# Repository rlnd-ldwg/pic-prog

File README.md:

# Programmer for 8-bit PIC devices built upon AVR (or Arduino)

For [Micro progmeter](https://github.com/jaromir-sukuba/micro_progmeter) project I want to deliver full set of open-source materials, but it would be shame if folks trying to replicate the project would have to buy another programmer to flash the PIC MCU, so I decided to do a little bit of brain stretching and implement PIC16F1xxx programmer with... Arduino. I really can't say I love this platform, but it is low cost and available.
Together with SDCC compiler this serves as completely open-source basis for many 8-bit PIC devices.

The current project status: Programmer working, sources need cleanup, perhaps rework of its structure (it grew out of its simple structure).
# List of supported devices is at the end of this page.

## Hardware
There are two options fo hardware for this project:

### Hardware option 1 - Arduino hardware
Take any Arduino with ATmega328P, like Uno or most of cheap chinese knock-off boards. Considering the target has its own power supply, connect GND, MCLR, PGC and PGD lines to respective pins on arduino as follows:

| Arduino pin | AVR pin | Target PIC pin | Comment                                                                     |
|-------------|---------|----------------|-----------------------------------------------------------------------------|
| GND         | GND     | GND            | common ground                                                               |
| 5V          | VDD     | VDD            | optional*- power supply for PIC MCU, you may power target from other source |
| A3          | PC3     | MCLR           | reset line of PIC MCU                                                       |
| A1          | PC1     | PGD            | programming data line                                                       |
| A0          | PC0     | PGC            | programming clock line                                                      |

* If you are powering target PIC from other power source (in circuit programming), series resistors (something like 470-1000 Ohms) in MCLR, PGC and PGD lines are good idea, it will somehow decrease currents flowing through IO pins due to power supplies differences between arduino and target board. In this configuration, even targets running at 3,3V are possible to program, though it is dirty practice.

Power it up, no smoke should be released. Run arduino IDE, open programmer firmware from here (/fw/pp.ino), complie and upload to arduino board - now you have PIC programmer ready to go. Go to software below.

The programmer is proven to work with some generic Uno board from china, as well as chinese arduino-nano clone

#### High Voltage Programming
Basically copied from https://github.com/rweather/ardpicprog and only implemented for Arduino Uno and `CF_P16F_A`. Needs the transistor and resistors from https://rweather.github.io/ardpicprog/pic14_zif_circuit.html (tested only for 16f1825: 9V block battery as power source, BC 337, 1k for the base and 10k for the emitter) and these connections to the Arduino:

| Arduino pin | AVR pin | Target pin / comment          |
|-------------|---------|-------------------------------|
| GND         | GND     | GND/VSS                       |
| A0          | PC0     | PGC                           |
| A1          | PC1     | PGD                           |
| A2          | PC2     | VDD                           |
| A4          | PC4     | MCLR transistor base resistor |

### Hardware option 2 - dedicated board
I designed this little board, see at /hw directory

Considering the target has its own power supply, connect GND, MCLR, PGC and PGD lines to respective pins on PIC programmer (notice the pinout similar to PICkit programmers). Vdd line is not currently used ad it is not needed for operation of programmer, but future revisions of firmware may take advantage of this pin and detect target VDD.
The hardware works with both FT232RL and CY7C65213 in place of USB/serial converter. Both were proven to work, with no other hardware difference.

Use [another arduino](https://www.arduino.cc/en/Tutorial/ArduinoISP) (or proper ISP programmer) to load Arduino UNO bootloader to PIC programmer board (performed only once), turning it into regular arduino compatible board.

Ensure JP2 is closed, then you can load new firmware into PIC programmer using regular Arduino IDE. Open jumper JP2. Now you have your programmer ready to go, move on to software.
The firmware should be able to compile outside Arduino IDE as it doesn't contain any Arduino-specific stuff, though I haven't tried that.

## Software

When running under Linux, download source from this repository and run

`gcc -Wall pp3.c -o pp3`

This should build executable pp3. When working under windows, you can download compiled binary from this repository. Alternatively, you can build it from source - install minGW and run

`gcc -Wall pp3.c -o pp3`

ie. the same procedure as on Linux. This should result in silent build with pp3.exe executable created.

Running the executable with no parameters should only bring banner "pp programmer". Though running with basic set of parameters

`./pp3 -c /dev/ttyACM0 -t 16f1829 file.hex`

under Linux, where -c parameter denotes port to be accessed, -t parameter defines PIC to be programmed and last parameter is hex file to be downloaded; or

`pp3.exe -c COM30 -t 16f1829 file.hex`

under Windows should program the target PIC; with expected result:

	$ ./pp3 -c /dev/ttyACM0 -t 16f1829 file.hex
    Opening serial port
    Device ID 0x27E4
    Programming FLASH (16384 B in 256 pages)
    Programming config
    Verifying FLASH (16384 B in 256 pages)
    Verifying config
    Releasing MCLR

## Notes on software

If you are running the hardware on generic arduino board or you forget to open jumper JP2 after loading firmware on dedicated hardware, you may need to insert waiting time after opening serial port and before communication - to ensure Arduino bootloader times out after opening serial port and takes control to programmer firmware. It should look like this

`pp3.exe -c COM30 -s 1700 -t 16f1829 file.bin`

where number after -s switch defines the number of miliseconds to wait after opening the serial port.

You may omit the actual programming using -p switch or verification using -n switch, when using both the programmer only checks target device signature and exits.

`$ ./pp3 -c /dev/ttyACM0 -p -n -t 16f1829 file.bin`

    Opening serial port
    Device ID 0x27E4
    Releasing MCLR

you can add some debug output info using -v parameter, ranging from -v 1 to -v 4. It may be suitable for debugging, -v 4 prints out all byte transaction on serial port, so be prepared for huge output.
There is database file pp3_devices.dat which hold information of supported PIC types. For now, the filename is fixed in code can't be changed and file has to be in the same directory as pp executable..

## Supported devices

Obviously, there is more supported than verified (tested) devices. I tried to test at least one device from specific family. The members from one family are usually very very similar, giving me enough confidence to mark them as supproted. Of course, typos can happen, but those are easy to correct.

**DEVICE**|**TESTED**
:-----:|:-----:
PIC12F1501|YES
PIC12F1571| 
PIC12F1572|YES
PIC12F1612|YES
PIC12F1822|YES
PIC12F1840|YES
PIC12LF1501|YES
PIC12LF1552|YES
PIC12LF1571| 
PIC12LF1572| 
PIC12LF1612| 
PIC12LF1822| 
PIC12LF1840|YES
PIC16F1454| 
PIC16F1455|YES
PIC16F1459| 
PIC16F1503|YES
PIC16F1507|YES
PIC16F1508| 
PIC16F1509|YES
PIC16F1512| 
PIC16F1513| 
PIC16F1516|YES
PIC16F1517| 
PIC16F1518| 
PIC16F1519| 
PIC16F1528| 
PIC16F1529| 
PIC16F15313| 
PIC16F15323| 
PIC16F15324| 
PIC16F15325| 
PIC16F15344| 
PIC16F15345| 
PIC16F15354| 
PIC16F15355|YES
PIC16F15356| 
PIC16F15375| 
PIC16F15376| 
PIC16F15385| 
PIC16F15386| 
PIC16F1574| 
PIC16F1575|YES
PIC16F1578| 
PIC16F1579| 
PIC16F1613|YES
PIC16F1614| 
PIC16F1615|YES
PIC16F1618| 
PIC16F1619|YES
PIC16F1703|YES
PIC16F1704| 
PIC16F1705| 
PIC16F1707| 
PIC16F1708| 
PIC16F1709| 
PIC16F1713| 
PIC16F1716| 
PIC16F1717| 
PIC16F1718|YES
PIC16F1719| 
PIC16F1764| 
PIC16F1765|YES
PIC16F1768| 
PIC16F1769| 
PIC16F1782| 
PIC16F1783|YES
PIC16F1784| 
PIC16F1786| 
PIC16F1787| 
PIC16F1788|YES
PIC16F1789| 
PIC16F1823|YES 
PIC16F1824| 
PIC16F1825|YES 
PIC16F1826| 
PIC16F1827| 
PIC16F1828| 
PIC16F1829|YES
PIC16F18313| 
PIC16F18323| 
PIC16F18324| 
PIC16F18325| 
PIC16F18326| 
PIC16F18344| 
PIC16F18345| 
PIC16F18346|YES
PIC16F18424| 
PIC16F18425| 
PIC16F18426| 
PIC16F18444| 
PIC16F18445| 
PIC16F18446| 
PIC16F18455| 
PIC16F18456| 
PIC16F1847| 
PIC16F18854| 
PIC16F18855|YES
PIC16F18856| 
PIC16F18857| 
PIC16F18875|YES
PIC16F18876| 
PIC16F18877| 
PIC16F19155| 
PIC16F19156|YES
PIC16F19175| 
PIC16F19176|YES
PIC16F19185| 
PIC16F19186| 
PIC16F19195| 
PIC16F19196| 
PIC16F19197| 
PIC16F1933|YES
PIC16F1934| 
PIC16F1936| 
PIC16F1937| 
PIC16F1938| 
PIC16F1939| 
PIC16F1946| 
PIC16F1947| 
PIC16LF1454| 
PIC16LF1455|YES
PIC16LF1459| 
PIC16LF1503|YES
PIC16LF1507| 
PIC16LF1508|YES
PIC16LF1509| 
PIC16LF1512| 
PIC16LF1513| 
PIC16LF1516| 
PIC16LF1517| 
PIC16LF1518| 
PIC16LF1519| 
PIC16LF1528| 
PIC16LF1529| 
PIC16LF15313| 
PIC16LF15323| 
PIC16LF15324| 
PIC16LF15325| 
PIC16LF15344| 
PIC16LF15345| 
PIC16LF15354| 
PIC16LF15355| 
PIC16LF15356| 
PIC16LF15375| 
PIC16LF15376| 
PIC16LF15385| 
PIC16LF15386| 
PIC16LF1574| 
PIC16LF1575| 
PIC16LF1578| 
PIC16LF1579| 
PIC16LF1613| 
PIC16LF1614| 
PIC16LF1615| 
PIC16LF1618| 
PIC16LF1619|
PIC16LF1703| 
PIC16LF1704|YES
PIC16LF1705| 
PIC16LF1707| 
PIC16LF1708| 
PIC16LF1709| 
PIC16LF1713|YES
PIC16LF1716| 
PIC16LF1717| 
PIC16LF1718| 
PIC16LF1719| 
PIC16LF1764| 
PIC16LF1765| 
PIC16LF1768| 
PIC16LF1769| 
PIC16LF1782| 
PIC16LF1783| 
PIC16LF1784| 
PIC16LF1786| 
PIC16LF1787| 
PIC16LF1788| 
PIC16LF1789| 
PIC16LF1824| 
PIC16LF1825| 
PIC16LF1826| 
PIC16LF1827| 
PIC16LF1828| 
PIC16LF1829|YES
PIC16LF18313| 
PIC16LF18323| 
PIC16LF18324| 
PIC16LF18325| 
PIC16LF18326| 
PIC16LF18344| 
PIC16LF18345| 
PIC16LF18346| 
PIC16LF18424| 
PIC16LF18425| 
PIC16LF18444| 
PIC16LF18445| 
PIC16LF18455| 
PIC16LF18456| 
PIC16LF1847| 
PIC16LF18854| 
PIC16LF18855| 
PIC16LF18856| 
PIC16LF18857| 
PIC16LF18875| 
PIC16LF18876| 
PIC16LF18877| 
PIC16LF1902| 
PIC16LF1903|YES
PIC16LF1904| 
PIC16LF1906| 
PIC16LF1907| 
PIC16LF19155| 
PIC16LF19156| 
PIC16LF19175| 
PIC16LF19176| 
PIC16LF19185| 
PIC16LF19186| 
PIC16LF19195| 
PIC16LF19196| 
PIC16LF19197| 
PIC16LF1933| 
PIC16LF1934| 
PIC16LF1936| 
PIC16LF1937| 
PIC16LF1938| 
PIC16LF1939| 
PIC16LF1946| 
PIC16LF1947| 
PIC18F23K22| 
PIC18F24J10|YES
PIC18F24J11| 
PIC18F24J50|YES
PIC18F24K22|YES
PIC18F24K40| 
PIC18F24K42| 
PIC18F24K50| 
PIC18F25J10| 
PIC18F25J11| 
PIC18F25J50| 
PIC18F25K22| 
PIC18F25K40| 
PIC18F25K42| 
PIC18F25K50|YES
PIC18F25K80|YES
PIC18F25Q10|YES
PIC18F26J11|YES
PIC18F26J13| 
PIC18F26J50|YES
PIC18F26J53| 
PIC18F26K22|YES
PIC18F26K40| 
PIC18F26K42| 
PIC18F26K50| 
PIC18F26K80| 
PIC18F26Q10| 
PIC18F27J13| 
PIC18F27J53|YES
PIC18F27K40| 
PIC18F27K42| 
PIC18F27Q10| 
PIC18F43K22| 
PIC18F44J10| 
PIC18F44J11| 
PIC18F44J50| 
PIC18F44K22| 
PIC18F45J10|YES
PIC18F45J11| 
PIC18F45J50| 
PIC18F45K22| 
PIC18F45K40| 
PIC18F45K42| 
PIC18F45K50| 
PIC18F45K80| 
PIC18F45Q10| 
PIC18F46J11| 
PIC18F46J13| 
PIC18F46J50| 
PIC18F46J53| 
PIC18F46K22| 
PIC18F46K40| 
PIC18F46K42| 
PIC18F46K50| 
PIC18F46K80| 
PIC18F46Q10| 
PIC18F47J13| 
PIC18F47J53| 
PIC18F47K40|YES
PIC18F47K42| 
PIC18F47Q10| 
PIC18F47Q43|YES
PIC18F47Q83|YES
PIC18F47Q84|YES
PIC18F55K42| 
PIC18F56K42| 
PIC18F57K42|YES
PIC18F63J11| 
PIC18F63J90| 
PIC18F64J11| 
PIC18F64J90| 
PIC18F65J10| 
PIC18F65J11| 
PIC18F65J15| 
PIC18F65J50| 
PIC18F65J90| 
PIC18F65J94| 
PIC18F65K22| 
PIC18F65K40| 
PIC18F65K80| 
PIC18F65K90| 
PIC18F66J10| 
PIC18F66J11| 
PIC18F66J15|YES
PIC18F66J16| 
PIC18F66J50| 
PIC18F66J55| 
PIC18F66J60| 
PIC18F66J65| 
PIC18F66J90| 
PIC18F66J93| 
PIC18F66J94| 
PIC18F66J99| 
PIC18F66K22| 
PIC18F66K40| 
PIC18F66K80| 
PIC18F66K90| 
PIC18F67J10| 
PIC18F67J11| 
PIC18F67J50|YES
PIC18F67J60| 
PIC18F67J90| 
PIC18F67J93| 
PIC18F67J94| 
PIC18F67K22|YES
PIC18F67K40| 
PIC18F67K90| 
PIC18F83J11| 
PIC18F83J90| 
PIC18F84J11| 
PIC18F84J90| 
PIC18F85J10| 
PIC18F85J11| 
PIC18F85J15| 
PIC18F85J50| 
PIC18F85J90| 
PIC18F85J94| 
PIC18F85K22| 
PIC18F85K90| 
PIC18F86J10| 
PIC18F86J11| 
PIC18F86J15| 
PIC18F86J16| 
PIC18F86J50| 
PIC18F86J55| 
PIC18F86J60| 
PIC18F86J65| 
PIC18F86J72| 
PIC18F86J90| 
PIC18F86J93| 
PIC18F86J94| 
PIC18F86J99| 
PIC18F86K22| 
PIC18F86K90| 
PIC18F87J10| 
PIC18F87J11| 
PIC18F87J50| 
PIC18F87J60| 
PIC18F87J72| 
PIC18F87J90| 
PIC18F87J93| 
PIC18F87J94| 
PIC18F87K22| 
PIC18F87K90| 
PIC18F95J94| 
PIC18F96J60| 
PIC18F96J65| 
PIC18F96J94| 
PIC18F96J99| 
PIC18F97J60| 
PIC18F97J94| 
PIC18LF23K22| 
PIC18LF24J10| 
PIC18LF24J11| 
PIC18LF24J50| 
PIC18LF24K22| 
PIC18LF24K40| 
PIC18LF24K42| 
PIC18LF24K50|YES
PIC18LF25J10| 
PIC18LF25J11| 
PIC18LF25J50| 
PIC18LF25K22|YES
PIC18LF25K40| 
PIC18LF25K42| 
PIC18LF25K50|YES
PIC18LF25K80| 
PIC18LF26J11| 
PIC18LF26J13| 
PIC18LF26J50| 
PIC18LF26J53| 
PIC18LF26K22| 
PIC18LF26K40| 
PIC18LF26K42| 
PIC18LF26K50| 
PIC18LF26K80| 
PIC18LF27J13| 
PIC18LF27J53| 
PIC18LF27K40| 
PIC18LF27K42| 
PIC18LF43K22| 
PIC18LF44J10| 
PIC18LF44J11| 
PIC18LF44J50| 
PIC18LF44K22| 
PIC18LF45J10| 
PIC18LF45J11| 
PIC18LF45J50| 
PIC18LF45K22| 
PIC18LF45K40| 
PIC18LF45K42| 
PIC18LF45K50| 
PIC18LF45K80| 
PIC18LF46J11| 
PIC18LF46J13| 
PIC18LF46J50| 
PIC18LF46J53| 
PIC18LF46K22| 
PIC18LF46K40| 
PIC18LF46K42| 
PIC18LF46K50| 
PIC18LF46K80| 
PIC18LF47J13| 
PIC18LF47J53| 
PIC18LF47K40| 
PIC18LF47K42| 
PIC18LF55K42| 
PIC18LF56K42| 
PIC18LF57K42| 
PIC18LF65K40| 
PIC18LF65K80| 
PIC18LF66K40| 
PIC18LF66K80| 
PIC18LF67K40| 

The whole project is licensed under MIT license, see LICENSE.md file.
Some more details to be found here https://hackaday.io/project/8559-pic16f1xxx-arduino-based-programmer

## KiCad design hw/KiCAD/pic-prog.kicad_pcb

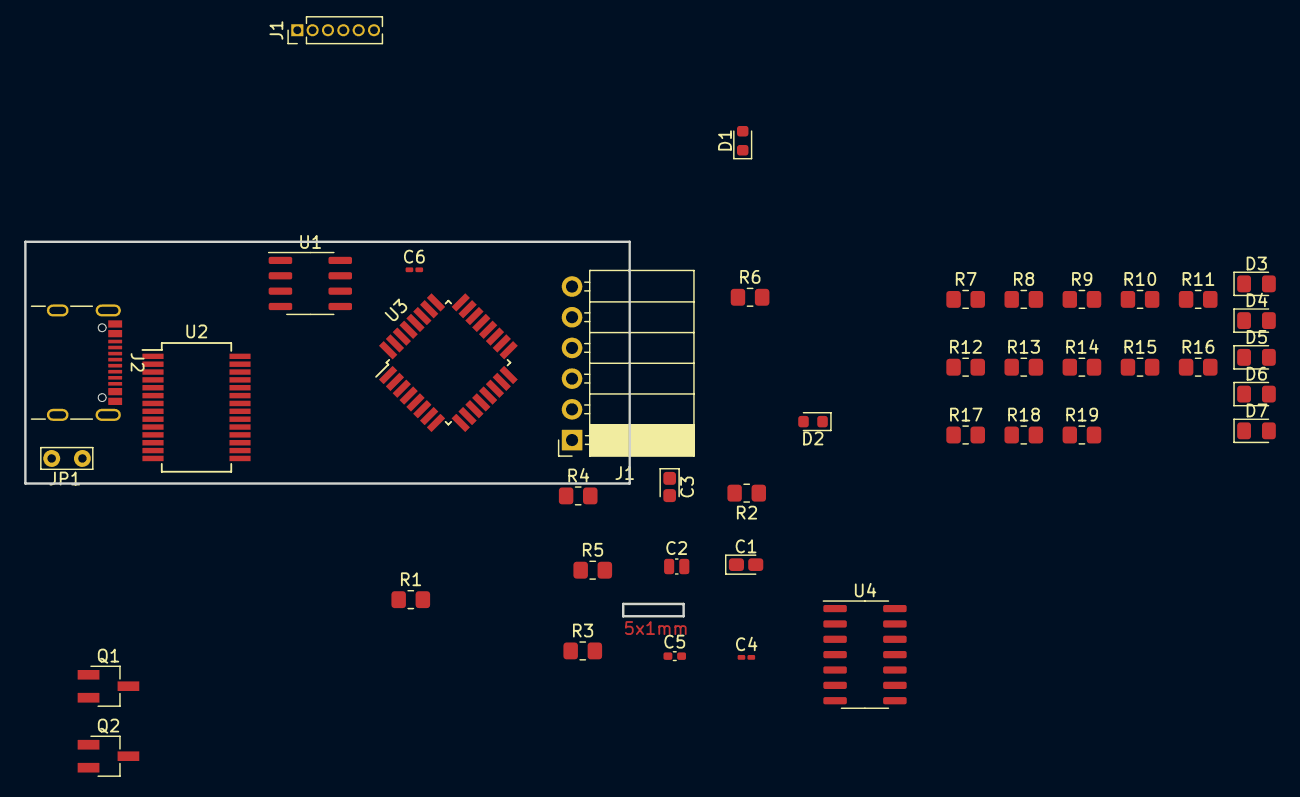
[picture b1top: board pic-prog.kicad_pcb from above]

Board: 2 copper layers, 42 parts (0 on the bottom side), 38 nets, no tracks yet.

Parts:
C1: 1µF; CP_EIA-1608-10_AVX-L_Pad1.25x1.05mm_HandSolder
C2: 1nF; C_0504_1310Metric_Pad0.83x1.28mm_HandSolder
C3: 1µF; CP_EIA-1608-08_AVX-J
C4: 100nF; C_0201_0603Metric_Pad0.64x0.40mm_HandSolder
C5: 100nF; C_0402_1005Metric_Pad0.74x0.62mm_HandSolder
C6: C; C_0201_0603Metric_Pad0.64x0.40mm_HandSolder
D1, D2: BAT43; D_0603_1608Metric
D3: Green; D_0805_2012Metric_Pad1.15x1.40mm_HandSolder
D4: Blue; D_0805_2012Metric_Pad1.15x1.40mm_HandSolder
D5: Red; D_0805_2012Metric_Pad1.15x1.40mm_HandSolder
D6: Orange; D_0805_2012Metric_Pad1.15x1.40mm_HandSolder
D7: White; D_0805_2012Metric_Pad1.15x1.40mm_HandSolder
J1: ICSP PIC; PinSocket_1x06_P2.54mm_Horizontal
J1#2: ISP AVR; PinHeader_1x06_P1.27mm_Vertical
J2: USB-C connector; USB_C_Receptacle_GCT_USB4105-xx-A_16P_TopMnt_Horizontal
JP1: bootloading; TestPoint_Bridge_Pitch2.54mm_Drill0.7mm
Q1, Q2: BS250; SC-59_Handsoldering
R1: 5k6; R_0805_2012Metric_Pad1.20x1.40mm_HandSolder
R2: 100; R_0805_2012Metric_Pad1.20x1.40mm_HandSolder
R3, R4, R7, R8, R9: 1k; R_0805_2012Metric_Pad1.20x1.40mm_HandSolder
R5, R6: 5k1; R_0805_2012Metric_Pad1.20x1.40mm_HandSolder
R10, R11, R12, R13: 470; R_0805_2012Metric_Pad1.20x1.40mm_HandSolder
R14, R15, R16, R17, R18, R19: R; R_0805_2012Metric_Pad1.20x1.40mm_HandSolder
U1: NE555D; SOIC-8_3.9x4.9mm_P1.27mm
U2: FT232RL; SSOP-28_5.3x10.2mm_P0.65mm
U3: ATmega328P-A; TQFP-32_7x7mm_P0.8mm
U4: 7403; SOIC-14_3.9x8.7mm_P1.27mm

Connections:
Gnd: C2.1, C2.2, C3.2, C4.2, D3.1 (K), J1.3, J1#2.6, J2.A1 (GND), J2.A12 (GND), J2.B1 (GND), J2.B12 (GND), J2.S1 (SHIELD), R1.1, R5.2, R6.2, R14.2, R18.2, U1.1 (GND), U1.2 (TR), U1.6 (THR), U2.7 (GND), U2.18 (GND), U2.21 (GND), U2.25 (AGND), U2.26 (TEST), U3.3 (GND), U3.5 (GND), U3.21 (GND), U4.7 (GND)
MCLR/Vpp: J1.1, Q1.1 (D), Q2.1 (D), R14.1
MISO: J1#2.1, U3.16 (PB4)
MOSI: J1#2.4, U3.15 (PB3)
unnamed: C1.2, R2.1
unnamed: C1.1, D1.1 (K), D2.2 (A)
unnamed: D3.2 (A), R7.2
unnamed: D4.2 (A), R8.1
unnamed: D4.1 (K), U2.22 (CBUS1)
unnamed: D5.2 (A), R9.1
unnamed: D5.1 (K), U2.23 (CBUS0)
unnamed: D6.1 (K), R17.1
unnamed: D7.1 (K), R18.1
unnamed: J2.A5 (CC1), R5.1
unnamed: J2.B5 (CC2), R6.1
unnamed: JP1.1 (A), U2.9 (DCR)
unnamed: Q1.2 (G), R16.2, U4.3
unnamed: R17.2, U4.2, U4.8
unnamed: R1.2, R2.2, U1.3 (Q)
unnamed: R4.1, U2.5 (RXD)
unnamed: R3.1, U2.1 (TXD)
unnamed: J2.A6 (D+), J2.B6 (D+), U2.15 (USBD+)
unnamed: J2.A7 (D-), J2.B7 (D-), U2.16 (USBD-)
unnamed: R3.2, U3.12 (PB0)
unnamed: R4.2, U3.13 (PB1)
unnamed: R10.1, U3.23 (PC0)
unnamed: R11.1, U3.24 (PC1)
unnamed: R12.1, U3.25 (PC2)
unnamed: R13.1, U3.26 (PC3)
PGC: J1.5, R10.2
PGD: J1.4, R11.2
PGM: J1.6, Q2.2 (G), R15.2, R19.2, U4.6, U4.11
Reset: C5.2, J1#2.5, U3.29 (~RESET/PC6)
SCK: J1#2.3, U3.17 (PB5)
Vcc: C4.1, D1.2 (A), D6.2 (A), J1.2, J1#2.2, J2.A4 (VBUS), J2.A9 (VBUS), J2.B4 (VBUS), J2.B9 (VBUS), Q1.3 (S), R7.1, R8.2, R9.2, R12.2, R15.1, R16.1, R19.1, U1.4 (R), U1.8 (VCC), U2.4 (VCCIO), U2.19 (~RESET), U2.20 (VCC), U3.4 (VCC), U3.6 (VCC), U3.18 (AVCC), U4.14 (VCC)
Vpp: C3.1, D2.1 (K), Q2.3 (S)
Vpp_on: D7.2 (A), U4.1, U4.4
Vpp_select: U4.5, U4.9, U4.10, U4.12, U4.13

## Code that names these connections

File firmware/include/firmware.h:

/*
 * firmware.h v1.0.0
 * 
 * Copyright October 2023 R.Ludwig
 * 
 * This program is free software; you can redistribute it and/or modify
 * it under the terms of the GNU General Public License as published by
 * the Free Software Foundation; either version 2 of the License, or
 * (at your option) any later version.
 * 
 * This program is distributed in the hope that it will be useful,
 * but WITHOUT ANY WARRANTY; without even the implied warranty of
 * MERCHANTABILITY or FITNESS FOR A PARTICULAR PURPOSE.  See the
 * GNU General Public License for more details.
 * 
 * You should have received a copy of the GNU General Public License
 * along with this program; if not, write to the Free Software
 * Foundation, Inc., 51 Franklin Street, Fifth Floor, Boston,
 * MA 02110-1301, USA.
 * 
 * constant and macro definition for main program
 * 
 * initial version 2023/10/26
 * 
 */
 
#ifndef FW_H
#define FW_H

#define ISP_PORT  PORTC
#define ISP_DDR   DDRC
#define ISP_PIN   PINC
#define ISP_CLK   0     // A0/PC0 PIC: programm clock (PGC)
#define ISP_DAT   1     // A1/PC1 PIC: programm data (PGD)
#define ISP_MCLR  3     // A3/PC3 PIC: reset (MCLR)
#define ISP_HVP_MCLR 4  // A4/PC4 PIC: VPP (same as MCLR Pin but for HVP - conversion necessary to use LVP and HPV together
#define ISP_HVP_VDD  2  // A2/PC2 PIC: VDD 

#define ISP_CLK_DELAY  1
#define _BAUD   57600   				// Baud rate (9600 is default)
#define _UBRR   (F_CPU/16)/_BAUD - 1	// Used for UBRRL and UBRRH 

#define ISP_MCLR_1 ISP_PORT |= (1<<ISP_MCLR);
#define ISP_MCLR_0 ISP_PORT &= ~(1<<ISP_MCLR);
#define ISP_MCLR_D_I ISP_DDR &= ~(1<<ISP_MCLR);
#define ISP_MCLR_D_0 ISP_DDR |= (1<<ISP_MCLR);

#define ISP_DAT_1 ISP_PORT |= (1<<ISP_DAT);
#define ISP_DAT_0 ISP_PORT &= ~(1<<ISP_DAT);
#define ISP_DAT_V (ISP_PIN&(1<<ISP_DAT))
#define ISP_DAT_D_I ISP_DDR &= ~(1<<ISP_DAT);
#define ISP_DAT_D_0 ISP_DDR |= (1<<ISP_DAT);

#define ISP_CLK_1 ISP_PORT |= (1<<ISP_CLK);
#define ISP_CLK_0 ISP_PORT &= ~(1<<ISP_CLK);
#define ISP_CLK_D_I ISP_DDR &= ~(1<<ISP_CLK);
#define ISP_CLK_D_0 ISP_DDR |= (1<<ISP_CLK);

#define ISP_HVP_MCLR_HV_OFF ISP_PORT |= (1<<ISP_HVP_MCLR); // inverted by transistor
#define ISP_HVP_MCLR_HV_ON ISP_PORT &= ~(1<<ISP_HVP_MCLR); // inverted by transistor
#define ISP_HVP_MCLR_D_I ISP_DDR &= ~(1<<ISP_HVP_MCLR);
#define ISP_HVP_MCLR_D_0 ISP_DDR |= (1<<ISP_HVP_MCLR);

#define ISP_HVP_VDD_ON ISP_PORT |= (1<<ISP_HVP_VDD);
#define ISP_HVP_VDD_OFF ISP_PORT &= ~(1<<ISP_HVP_VDD);
#define ISP_HVP_VDD_D_I ISP_DDR &= ~(1<<ISP_HVP_VDD);
#define ISP_HVP_VDD_D_0 ISP_DDR |= (1<<ISP_HVP_VDD);

#endif

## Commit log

2023-03-12 Add PIC 18F47Q43 and 18F47Q84 functions
    These changes are based on satoshiokue's work.
    See commit e233817f2a24 on the main branch on the repository
    https://github.com/satoshiokue/Arduino-PIC-Programmer.
2023-03-12 Add PIC 18F47Q43 and 18F47Q84
    These changes are based on satoshiokue's work.
    See commit e233817f2a24 on the main branch on the repository
    https://github.com/satoshiokue/Arduino-PIC-Programmer.
2023-03-12 Increase isp writing delay for PIC 18F47Qxx
    These changes are based on satoshiokue's work.
    See commit e233817f2a24 on the main branch on the repository
    https://github.com/satoshiokue/Arduino-PIC-Programmer.
2023-03-12 Add 18F47Q43 and 18F47Q84 to the supported device list
2023-03-25 Fix indent (cosmetic change)
2023-03-25 Abort if given input file has an error
2023-03-25 Add Arduino Leonardo board support
2023-03-25 Add 5 us delay in p18*_write_page() for Arduino Leonardo
2023-03-25 Add -r option to reset target before programming
2023-03-25 Acquire/release DAT and CLK lines in enter/exit progmode
2023-03-25 Suppress compile warnings
2023-03-25 Tweak Makefiles to build on Mac
2023-06-24 support high voltage programming
2023-10-25 Command file, include path for pio
2023-10-26 introduction of constants for commands / changed "if" statements to "switch"
2023-10-27 adapting pio configuration
2023-10-27 serial interface modifications
2023-10-29 Doku, adap firmware programm for platformIO
2023-11-05 new hardware interface - not yet tested
2023-11-05 cosmetic change in source code
2023-11-05 changed directory name
2023-11-27 Docu
